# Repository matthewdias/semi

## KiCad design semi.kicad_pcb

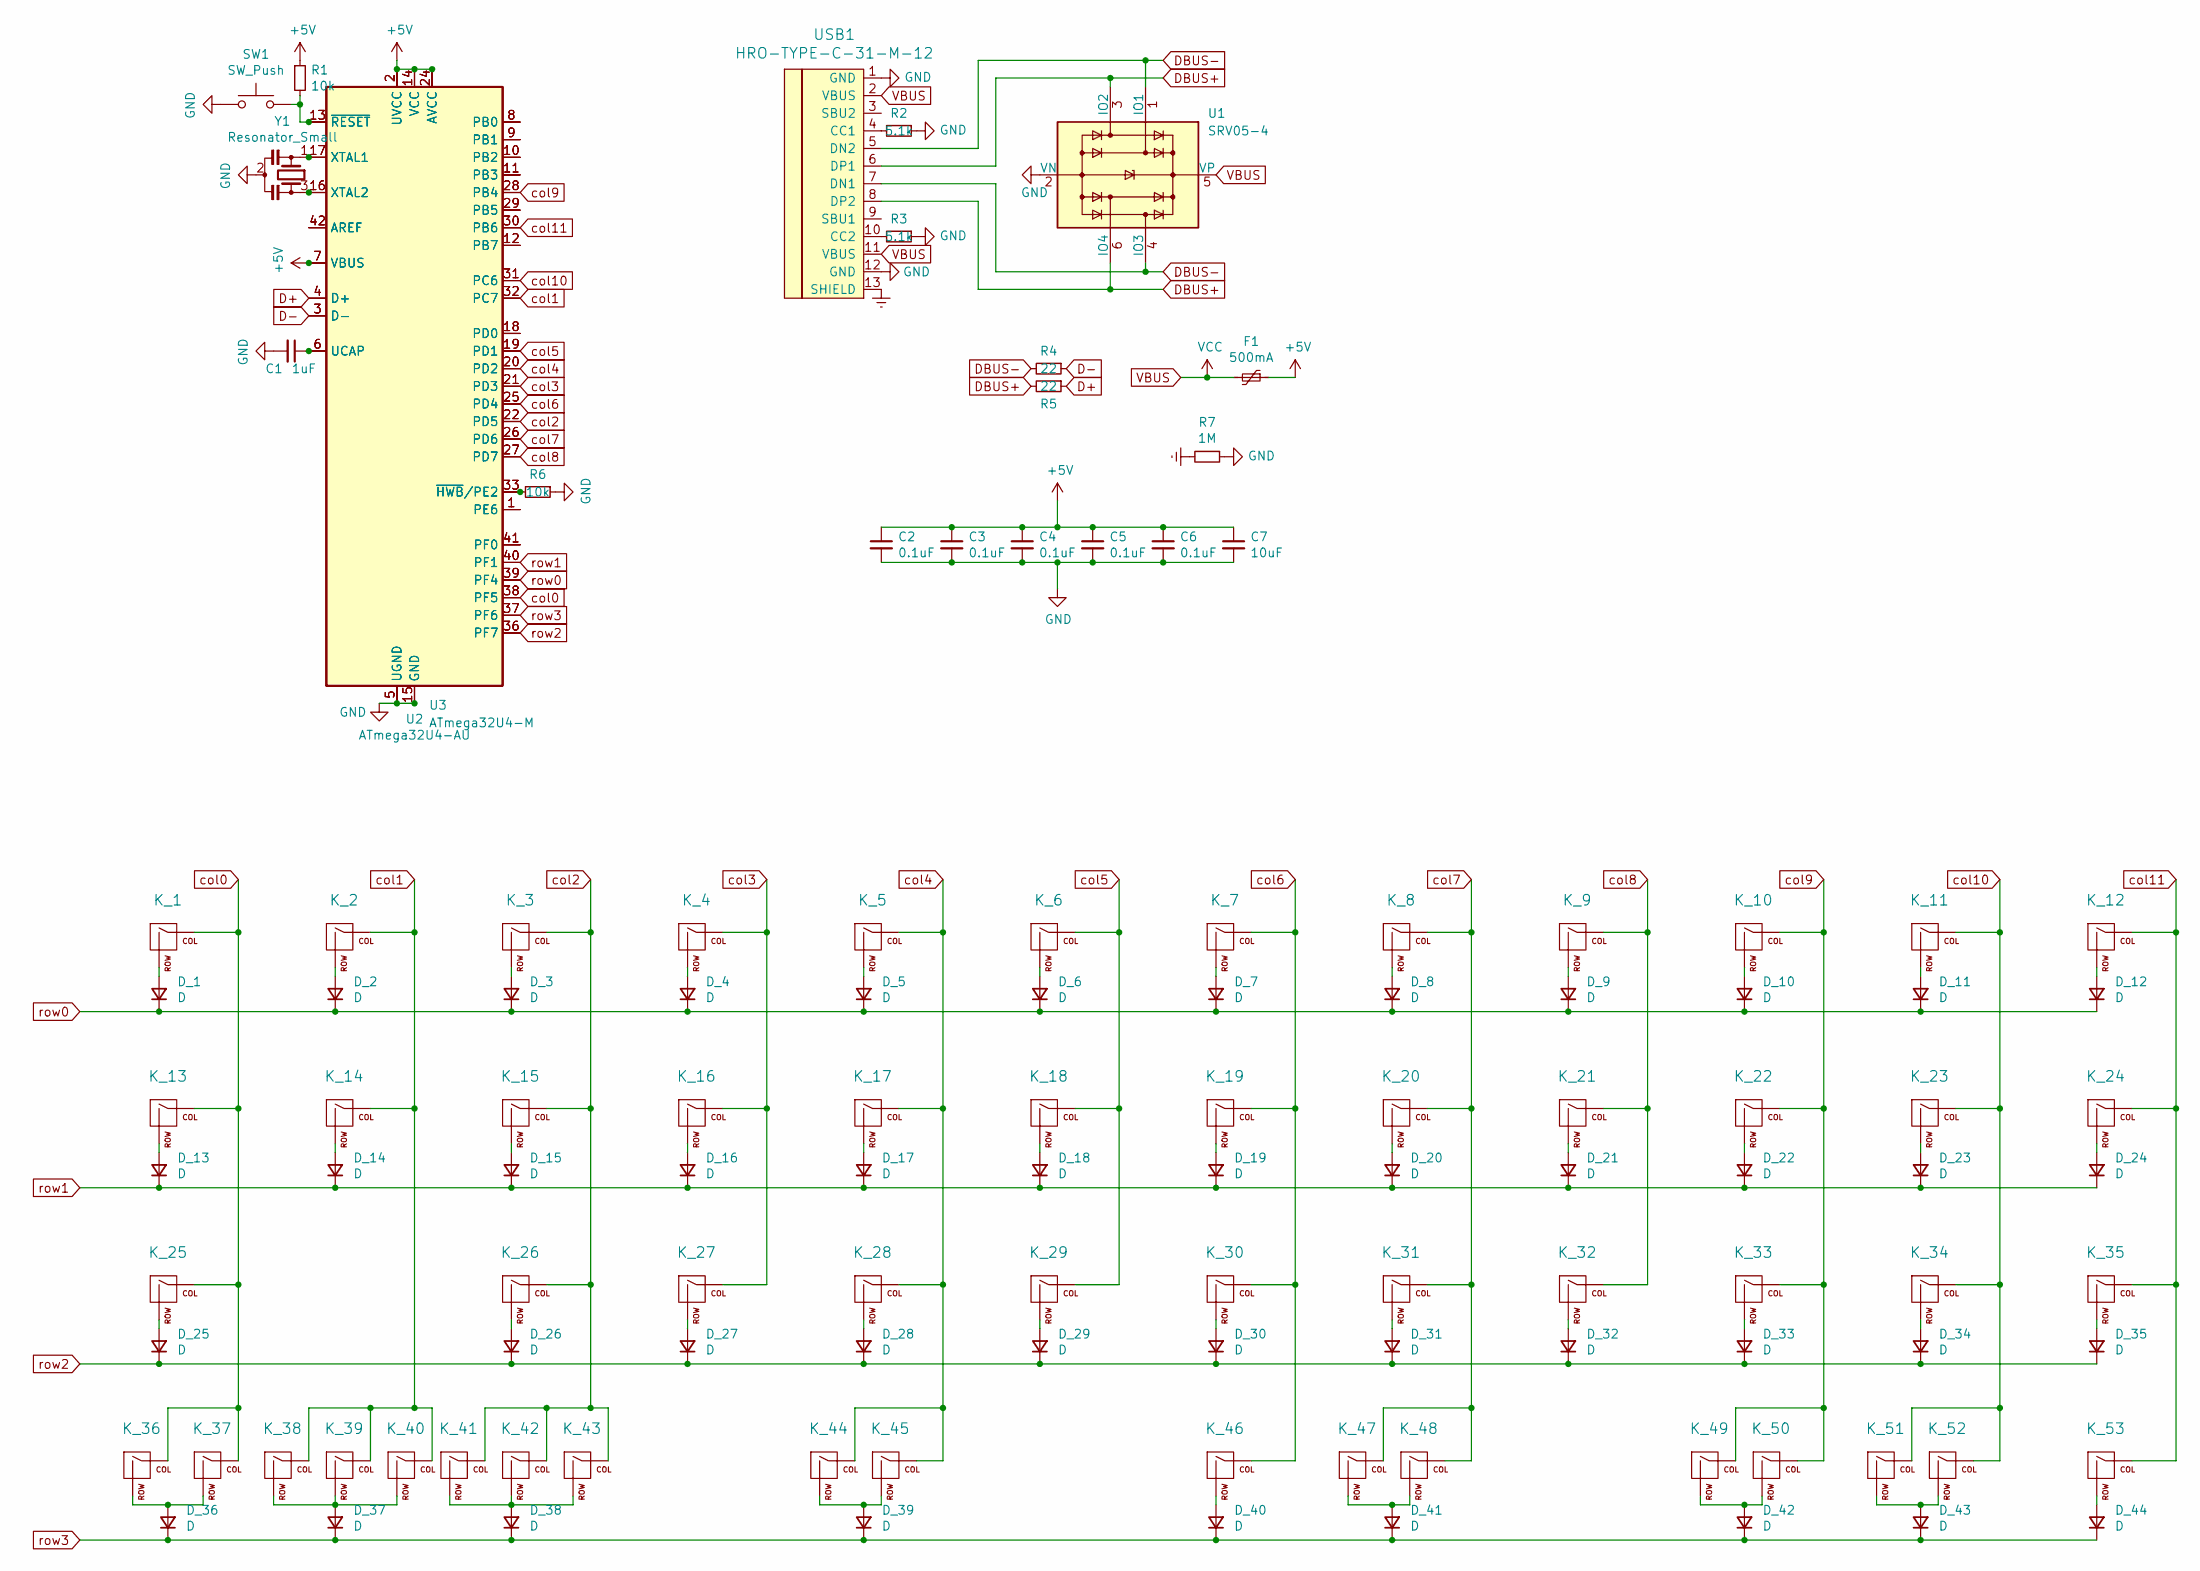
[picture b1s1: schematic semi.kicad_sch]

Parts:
C1: 1uF; C_0603_1608Metric
C2, C3, C4, C5, C6: 0.1uF; C_0603_1608Metric
C7: 10uF; C_0603_1608Metric
D_1, D_2, D_3, D_4, D_5, D_6, D_7, D_8, D_9, D_10, D_11, D_12, D_13, D_14, D_15, D_16, D_17, D_18, D_19, D_20, D_21, D_22, D_23, D_24, D_25, D_26, D_27, D_28, D_29, D_30, D_31, D_32, D_33, D_34, D_35, D_36, D_37, D_38, D_39, D_40, D_41, D_42, D_43, D_44: D; D_SOD-123
F1: 500mA; Fuse_1206_3216Metric
K_1, K_2, K_3, K_4, K_5, K_6, K_7, K_8, K_9, K_10, K_11, K_14, K_15, K_16, K_17, K_18, K_19, K_20, K_21, K_22, K_23, K_24, K_26, K_27, K_28, K_29, K_30, K_31, K_32, K_33, K_34, K_36, K_38, K_40, K_41, K_42, K_49, K_50, K_52, K_53: KEYSW; MXOnly-1U-NoLED
K_12, K_13, K_37, K_39, K_43, K_51: KEYSW; MXOnly-1.25U-NoLED
K_25: KEYSW; MXOnly-1.75U-NoLED
K_35: KEYSW; MXOnly-1.5U-NoLED
K_44, K_48: KEYSW; MXOnly-3U-ReversedStabilizers-NoLED
K_45, K_47: KEYSW; MXOnly-2.75U-ReversedStabilizers-NoLED
K_46: KEYSW; MXOnly-6.25U-ReversedStabilizers-NoLED
R1, R6: 10k; R_0603_1608Metric
R2, R3: 5.1k; R_0603_1608Metric
R4, R5: 22; R_0603_1608Metric
R7: 1M; R_0603_1608Metric
SW1: SW_Push; SKQG-1155865
U1: SRV05-4; SOT-23-6
U2: ATmega32U4-AU; TQFP-44_10x10mm_P0.8mm
U3: ATmega32U4-M; QFN-44-1EP_7x7mm_P0.5mm_EP5.2x5.2mm
USB1: HRO-TYPE-C-31-M-12; HRO-TYPE-C-31-M-12-Assembly
Y1: Resonator_Small; Resonator_SMD_muRata_CSTxExxV-3Pin_3.0x1.1mm

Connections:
+5V: C2.1, C3.1, C4.1, C5.1, C6.1, C7.1, F1.1, R1.1, U2.2 (UVCC), U2.7 (VBUS), U2.14 (VCC), U2.24 (AVCC), U2.34 (VCC), U2.44 (AVCC), U3.2 (UVCC), U3.7 (VBUS), U3.14 (VCC), U3.24 (AVCC), U3.34 (VCC), U3.44 (AVCC)
D+: R5.1, U2.4 (D+), U3.4 (D+)
D-: R4.1, U2.3 (D-), U3.3 (D-)
DBUS+: R5.2, U1.3 (IO2), U1.6 (IO4), USB1.6 (DP1), USB1.8 (DP2)
DBUS-: R4.2, U1.1 (IO1), U1.4 (IO3), USB1.5 (DN2), USB1.7 (DN1)
Earth: R7.2, USB1.13 (SHIELD)
GND: C1.2, C2.2, C3.2, C4.2, C5.2, C6.2, C7.2, R2.1, R3.1, R6.1, R7.1, SW1.1, U1.2 (VN), U2.5 (UGND), U2.15 (GND), U2.23 (GND), U2.35 (GND), U2.43 (GND), U3.5 (UGND), U3.15 (GND), U3.23 (GND), U3.35 (GND), U3.43 (GND), U3.45 (GND), USB1.1 (GND), USB1.12 (GND), Y1.2
unnamed: C1.1, U2.6 (UCAP), U3.6 (UCAP)
unnamed: D_1.2 (A), K_1.2 (ROW)
unnamed: D_2.2 (A), K_2.2 (ROW)
unnamed: D_3.2 (A), K_3.2 (ROW)
unnamed: D_4.2 (A), K_4.2 (ROW)
unnamed: D_5.2 (A), K_5.2 (ROW)
unnamed: D_6.2 (A), K_6.2 (ROW)
unnamed: D_7.2 (A), K_7.2 (ROW)
unnamed: D_8.2 (A), K_8.2 (ROW)
unnamed: D_9.2 (A), K_9.2 (ROW)
unnamed: D_10.2 (A), K_10.2 (ROW)
unnamed: D_11.2 (A), K_11.2 (ROW)
unnamed: D_12.2 (A), K_12.2 (ROW)
unnamed: D_13.2 (A), K_13.2 (ROW)
unnamed: D_14.2 (A), K_14.2 (ROW)
unnamed: D_15.2 (A), K_15.2 (ROW)
unnamed: D_16.2 (A), K_16.2 (ROW)
unnamed: D_17.2 (A), K_17.2 (ROW)
unnamed: D_18.2 (A), K_18.2 (ROW)
unnamed: D_19.2 (A), K_19.2 (ROW)
unnamed: D_20.2 (A), K_20.2 (ROW)
unnamed: D_21.2 (A), K_21.2 (ROW)
unnamed: D_22.2 (A), K_22.2 (ROW)
unnamed: D_23.2 (A), K_23.2 (ROW)
unnamed: D_24.2 (A), K_24.2 (ROW)
unnamed: D_25.2 (A), K_25.2 (ROW)
unnamed: D_26.2 (A), K_26.2 (ROW)
unnamed: D_27.2 (A), K_27.2 (ROW)
unnamed: D_28.2 (A), K_28.2 (ROW)
unnamed: D_29.2 (A), K_29.2 (ROW)
unnamed: D_30.2 (A), K_30.2 (ROW)
unnamed: D_31.2 (A), K_31.2 (ROW)
unnamed: D_32.2 (A), K_32.2 (ROW)
unnamed: D_33.2 (A), K_33.2 (ROW)
unnamed: D_34.2 (A), K_34.2 (ROW)
unnamed: D_35.2 (A), K_35.2 (ROW)
unnamed: D_36.2 (A), K_36.2 (ROW), K_37.2 (ROW)
unnamed: D_37.2 (A), K_38.2 (ROW), K_39.2 (ROW), K_40.2 (ROW)
unnamed: D_38.2 (A), K_41.2 (ROW), K_42.2 (ROW), K_43.2 (ROW)
unnamed: D_39.2 (A), K_44.2 (ROW), K_45.2 (ROW)
unnamed: D_40.2 (A), K_46.2 (ROW)
unnamed: D_41.2 (A), K_47.2 (ROW), K_48.2 (ROW)
unnamed: D_42.2 (A), K_49.2 (ROW), K_50.2 (ROW)
unnamed: D_43.2 (A), K_51.2 (ROW), K_52.2 (ROW)
unnamed: D_44.2 (A), K_53.2 (ROW)
unnamed: R1.2, SW1.2, U2.13 (~RESET), U3.13 (~RESET)
unnamed: R2.2, USB1.4 (CC1)
unnamed: R3.2, USB1.10 (CC2)
unnamed: R6.2, U2.33 (~HWB/PE2), U3.33 (~HWB/PE2)
unnamed: U2.1 (PE6), U3.1 (PE6)
unnamed: U2.8 (PB0), U3.8 (PB0)
unnamed: U2.9 (PB1), U3.9 (PB1)
unnamed: U2.10 (PB2), U3.10 (PB2)
unnamed: U2.11 (PB3), U3.11 (PB3)
unnamed: U2.12 (PB7), U3.12 (PB7)
unnamed: U2.16 (XTAL2), U3.16 (XTAL2), Y1.3
unnamed: U2.17 (XTAL1), U3.17 (XTAL1), Y1.1
unnamed: U2.18 (PD0), U3.18 (PD0)
unnamed: U2.29 (PB5), U3.29 (PB5)
unnamed: U2.41 (PF0), U3.41 (PF0)
unnamed: U2.42 (AREF), U3.42 (AREF)
VBUS: F1.2, U1.5 (VP), USB1.2 (VBUS), USB1.11 (VBUS)
col0: K_1.1 (COL), K_13.1 (COL), K_25.1 (COL), K_36.1 (COL), K_37.1 (COL), U2.38 (PF5), U3.38 (PF5)
col1: K_2.1 (COL), K_14.1 (COL), K_38.1 (COL), K_39.1 (COL), K_40.1 (COL), U2.32 (PC7), U3.32 (PC7)
col2: K_3.1 (COL), K_15.1 (COL), K_26.1 (COL), K_41.1 (COL), K_42.1 (COL), K_43.1 (COL), U2.22 (PD5), U3.22 (PD5)
col3: K_4.1 (COL), K_16.1 (COL), K_27.1 (COL), U2.21 (PD3), U3.21 (PD3)
col4: K_5.1 (COL), K_17.1 (COL), K_28.1 (COL), K_44.1 (COL), K_45.1 (COL), U2.20 (PD2), U3.20 (PD2)
col5: K_6.1 (COL), K_18.1 (COL), K_29.1 (COL), U2.19 (PD1), U3.19 (PD1)
col6: K_7.1 (COL), K_19.1 (COL), K_30.1 (COL), K_46.1 (COL), U2.25 (PD4), U3.25 (PD4)
col7: K_8.1 (COL), K_20.1 (COL), K_31.1 (COL), K_47.1 (COL), K_48.1 (COL), U2.26 (PD6), U3.26 (PD6)
col8: K_9.1 (COL), K_21.1 (COL), K_32.1 (COL), U2.27 (PD7), U3.27 (PD7)
col9: K_10.1 (COL), K_22.1 (COL), K_33.1 (COL), K_49.1 (COL), K_50.1 (COL), U2.28 (PB4), U3.28 (PB4)
col10: K_11.1 (COL), K_23.1 (COL), K_34.1 (COL), K_51.1 (COL), K_52.1 (COL), U2.31 (PC6), U3.31 (PC6)
col11: K_12.1 (COL), K_24.1 (COL), K_35.1 (COL), K_53.1 (COL), U2.30 (PB6), U3.30 (PB6)
row0: D_1.1 (K), D_2.1 (K), D_3.1 (K), D_4.1 (K), D_5.1 (K), D_6.1 (K), D_7.1 (K), D_8.1 (K), D_9.1 (K), D_10.1 (K), D_11.1 (K), D_12.1 (K), U2.39 (PF4), U3.39 (PF4)
row1: D_13.1 (K), D_14.1 (K), D_15.1 (K), D_16.1 (K), D_17.1 (K), D_18.1 (K), D_19.1 (K), D_20.1 (K), D_21.1 (K), D_22.1 (K), D_23.1 (K), D_24.1 (K), U2.40 (PF1), U3.40 (PF1)
row2: D_25.1 (K), D_26.1 (K), D_27.1 (K), D_28.1 (K), D_29.1 (K), D_30.1 (K), D_31.1 (K), D_32.1 (K), D_33.1 (K), D_34.1 (K), D_35.1 (K), U2.36 (PF7), U3.36 (PF7)
row3: D_36.1 (K), D_37.1 (K), D_38.1 (K), D_39.1 (K), D_40.1 (K), D_41.1 (K), D_42.1 (K), D_43.1 (K), D_44.1 (K), U2.37 (PF6), U3.37 (PF6)

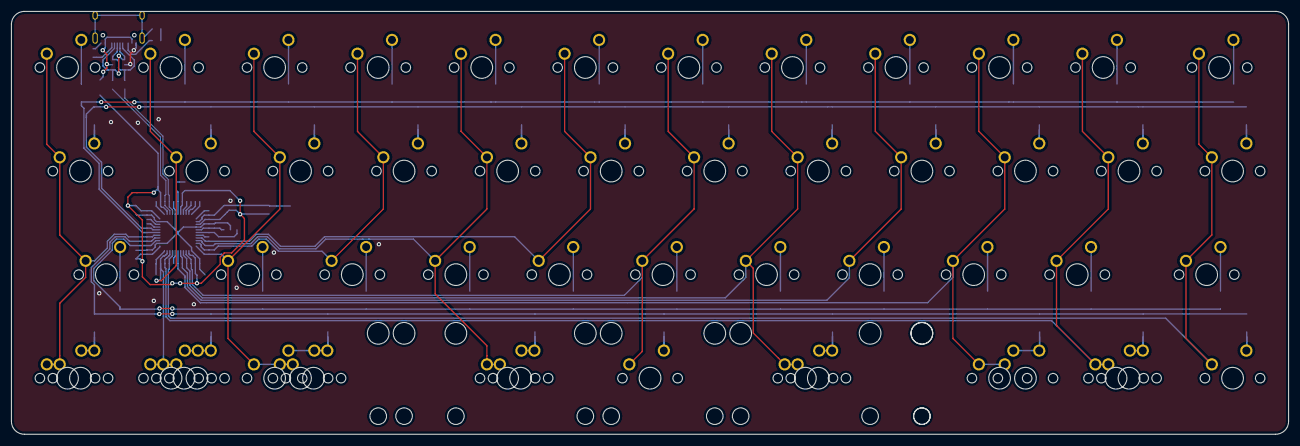
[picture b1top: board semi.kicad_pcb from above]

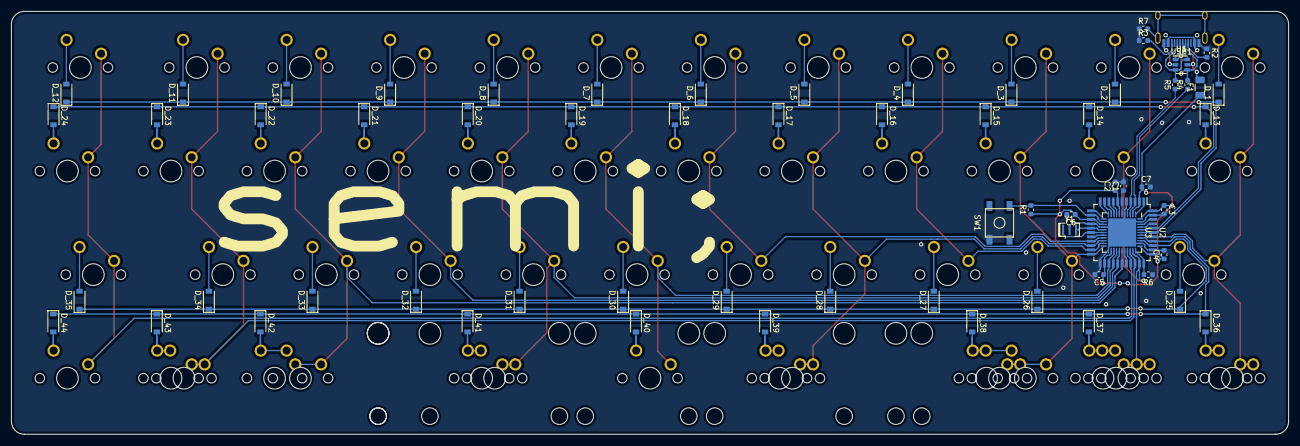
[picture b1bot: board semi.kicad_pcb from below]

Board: 2 copper layers, 234.9 x 77.8 mm, 118 parts (65 on the bottom side), 85 nets.

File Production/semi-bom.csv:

Designator,Quantity,Value,Footprint,LCSC Part #
"C1, ",1,1uF,603,C15849
"C4, C3, C2, C5, C6, ",5,0.1uF,603,C14663
"C7, ",1,10uF,603,C19702
"D_2, D_3, D_4, D_5, D_6, D_7, D_8, D_9, D_10, D_11, D_12, D_13, D_14, D_15, D_16, D_17, D_18, D_19, D_20, D_21, D_22, D_23, D_24, D_25, D_26, D_27, D_28, D_29, D_30, D_31, D_32, D_33, D_34, D_35, D_36, D_37, D_38, D_39, D_40, D_41, D_42, D_43, D_44, D_1, ",44,D,SOD-123,C64898
"F1, ",1,500mA,1206,C70076
"R2, R3, ",2,5.1k,603,C23186
"R5, R4, ",2,22,603,C23345
"R6, R1, ",2,10k,603,C25804
"R7, ",1,1M,603,C22935
"SW1, ",1,SW_Push,SMD,C318884
"U1, ",1,SRV05-4,SOT-23-6,C85364
"U3,",1,QFN-44-1EP_7x7mm_P0.5mm_EP5.2x5.2mm,ATmega32U4-M,C112161
"Y1, ",1,Resonator_Small,SMD,C341521

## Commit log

2021-01-09 Add images
2021-01-09 Hide refs
2021-01-14 Add model
2021-01-14 Add plate
2022-12-04 Updated PCB & Fixes
    Removed nonfunctional screw holes
    Added 32u4-MU footprint
    Updated PCB files to KiCad 6
    Updated production files to match
2022-12-04 Fixed README images
